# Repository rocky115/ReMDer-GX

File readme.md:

## Om Sree Sree Ganeshay Namoh
## Om Sree Sree Hanumate Namoh
## Om Sree Sree Akhandalamaneih Namoh

This repository is for building blocks, design, ideas and program for building graphics processing engine from scratch.

1. Folllow the exising benchmarks Nvidia, AMD, Intel

2. Guide- Render Hell !!

3. Gurus- QSoc amd Psytech . Go and work there.

4. Dylan_Berrie_FurryGPU - it seems to be an another Dylan. Nice and neat work. You must try it.

5. Another resource - "I built my own graphics card" - From JDH  It is also a good one. Continue and work hard.

6. You can refer to this work also - http://ethesis.nitrkl.ac.in/4342/1/u.pdf

4.
# 1. RMDON-INSIDE_DEEP_BLUE
Let us start on this Teacher's Day 2024

ALU - unit

##  2. Memory module cache has been added and common module has been assembled

Verify it and assemble it to test it.

3. Control logic added but not tested so far.

## Add control logic after a long time (2026)
See the referred work folder
(Comments IITm is doing well and steady work). Refer FurryGPU too and videos inside video folder.

## These are hopelessly lazy
We are  not getting time.Good luck. 

I hope we can start from here. It will be a roller and rocker. Let us see.

Wish you a great day :)

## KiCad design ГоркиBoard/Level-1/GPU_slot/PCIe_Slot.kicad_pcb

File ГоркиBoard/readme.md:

## Om Sree Sree Ganeshay Namoh
## Om Sree Sree Hanumate Namoh
## Om Sree Sree Akhandalamaneih Namoh

Inspired from Swadeshi movement - this repository is for building blocks, design, ideas and program for building hardware unit.

1. Folllow the exising benchmarks Nvidia, TMsc

2. It is a collborative effort from thousand of researchers, engineers and small children.

3. You can refer to pilot work also - http://ethesis.nitrkl.ac.in/4342/1/u.pdf

# 1. PCIC e slot with Chipset (Test them)

Currently only schematic is available. Day by day other module(verified) will be added gradually,

Suggestions and contributions are welcome

Email address-  rmdi115@gmail.com

### Special Notes
This has been already started. A lot of work has been dobe abd even gone for fabrication. Some materials have been also refrerred from them. Best of wishes and prayers for their work. It is a very good initiative you can start on witg it.It will be a roller and rocker and fun. Let us see.

Wish you a great day :)

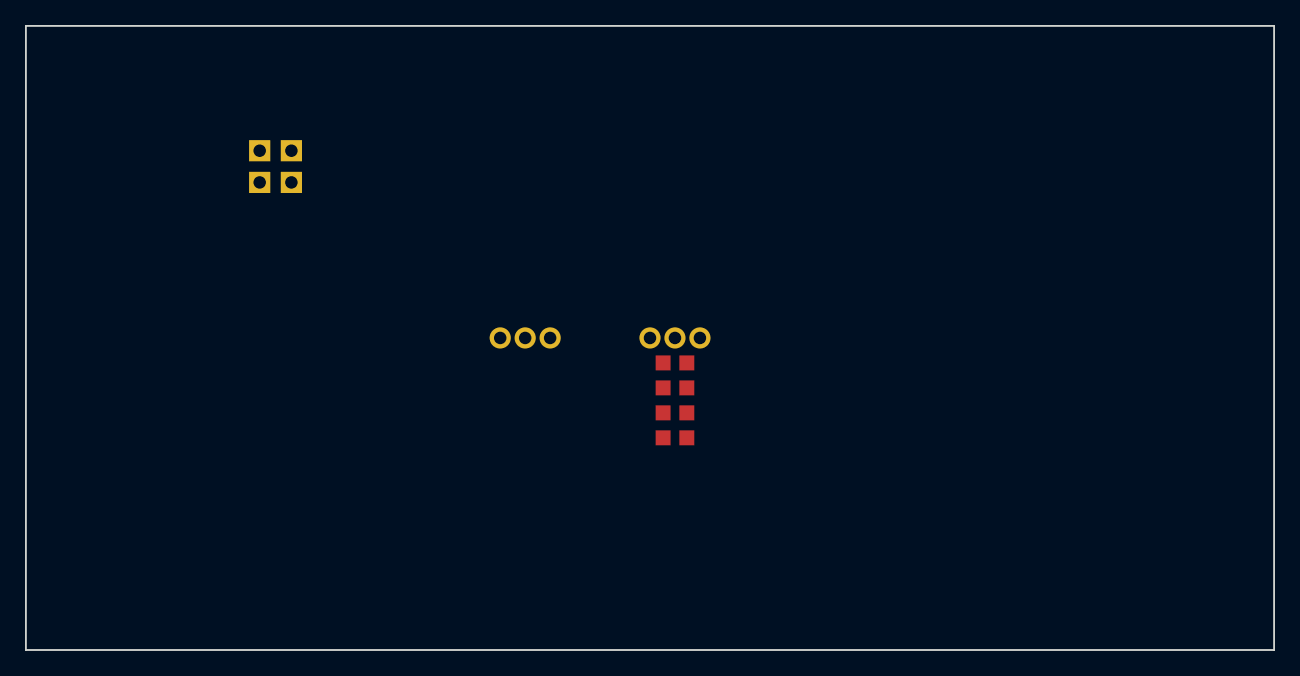
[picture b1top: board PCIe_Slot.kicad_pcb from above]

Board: 4 copper layers, 100.0 x 50.0 mm, 6 parts (0 on the bottom side), 3 nets.

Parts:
C1, C2, C3, C4: 10uF; C_0805_2012Metric
J1: PCIE_164
P1: Conn_02x02_Pin; PinHeader_2x02_P2.54mm_Vertical

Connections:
3V3: C2.1, C4.1, J1.B1, P1.2
12V: C1.1, C3.1, J1.A5, P1.1
GND: C1.2, C2.2, C3.2, C4.2, J1.A4, P1.3, P1.4

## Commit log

2024-07-20 Chapter-1 A Survey - where you are and what ancestors had done so far
2024-09-06 RMDON-BLUESTONE
2024-10-08 memory and common module assemble and verification
2025-02-23 Ccomputing and execution component
2025-03-27 Basic start tutorials
2025-04-09 New work reference by rmd
2025-08-02 Level-1 Gorkiboard design-- THe schematic
2026-03-02 Control
2026-03-14 FAB process challenges in India
2026-03-14 FAB process challenges in India-more
2026-03-14 FAB process challenges in India- tutorials-1
2026-03-14 Introduction-to-lithography-Fantastic-works
2026-03-14 IC-FAB-process-Fantastic-works
